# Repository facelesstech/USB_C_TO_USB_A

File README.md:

# USB_C_TO_USB_A
USB_C_TO_USB_A

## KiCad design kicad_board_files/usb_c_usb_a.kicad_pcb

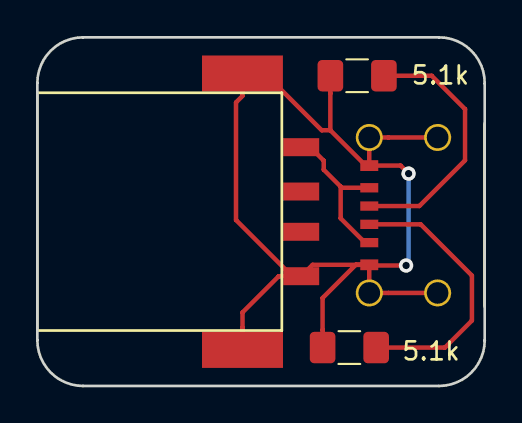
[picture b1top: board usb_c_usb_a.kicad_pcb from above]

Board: 2 copper layers, 24.9 x 19.4 mm, 4 parts (0 on the bottom side), 4 nets.

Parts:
5.1k, 5.1k#2: R; R_1206_3216Metric_Pad1.42x1.75mm_HandSolder
J1: USB_A; female_usb_custom_smd
U1: usb_c_6pin; USB_C_6PIN_custom

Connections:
unnamed: J1.1, U1.2
unnamed: 5.1k.1, 5.1k#2.1, J1.4, J1.5, U1.1
unnamed: 5.1k.2, U1.3
unnamed: 5.1k#2.2, U1.4

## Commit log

2019-11-02 board files
